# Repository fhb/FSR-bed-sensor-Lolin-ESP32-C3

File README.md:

# FSR-bed-sensor-Lolin-ESP32-C3
This project includes everything needed to build a bed occupancy sensor inspired by https://community.home-assistant.io/t/fsr-the-best-bed-occupancy-sensor/365795:
One PCB design for connecting two FSR sensors to an Lolin ESP32-C3 pico (pin compatible to Lolin ESP32-C3 mini) and a case for it. There are also two options to add a temperature sensor using the I2c port on the Lolin ESP32-C3. Everything has been tested and works. Make sure the JST-XH plugs are properly plugged in. 

List of materials:

* 2x JST_XH 2 pins male + female connector
* 1x Wemos Lolin ESP32-C3 pico
* 2x 8er Pinleiste
* 2x 8er Buchsenleiste
* 2x RM063 Potentiometer (V2)
* 2x FSR SF15-600 10kg

Option 1:The Wemos SHT-30 is the easiest option as ready made SH1.0 4Pin cables are available, that's the option I ended up using and designing a case for.
* 1x Wemos SHT-30 (https://www.wemos.cc/en/latest/d1_mini_shield/sht30.html)
* I2C Cable 10cm für LOLIN (WEMOS) SH1.0 4Pins

Option 2: You could also make your own JST-XH to JST-SH1.0 cable and solder a JST-XH connector to a BME280 5V Board. 
* JST-SH1.0 male connector --- 4 wire ---  JST-XH female + male connector 
* BME280 5V Board (I2C)

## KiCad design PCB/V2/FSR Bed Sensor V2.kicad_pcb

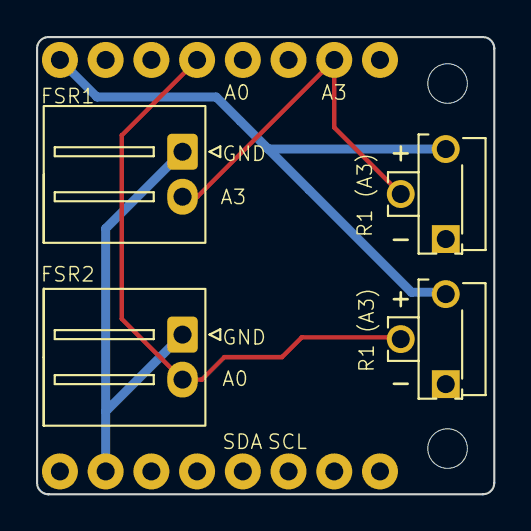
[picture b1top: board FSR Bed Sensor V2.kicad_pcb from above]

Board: 2 copper layers, 25.4 x 25.4 mm, 5 parts (0 on the bottom side), 4 nets.

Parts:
FSR1: ST_XH_S2B-XH-A-1_1x02_P2.50mm_Horizontal; JST_XH_S2B-XH-A-1_1x02_P2.50mm_Horizontal
FSR2: JST_XH_S2B-XH-A-1_1x02_P2.50mm_Horizontal
R1 (A3), R1 (A3)#2: Potentiometer_Runtron_RM-063_Horizontal
Wemos LOLIN C3 Pico: ESP32-C3; WEMOS_Lolin_ESP32-C3_Pico

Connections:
3.3V: R1 (A3).1, R1 (A3)#2.1, Wemos LOLIN C3 Pico.8
A0: FSR2.2, R1 (A3).2, Wemos LOLIN C3 Pico.5
A3: FSR1.2, R1 (A3)#2.2, Wemos LOLIN C3 Pico.2
GND: FSR1.1, FSR2.1, Wemos LOLIN C3 Pico.10

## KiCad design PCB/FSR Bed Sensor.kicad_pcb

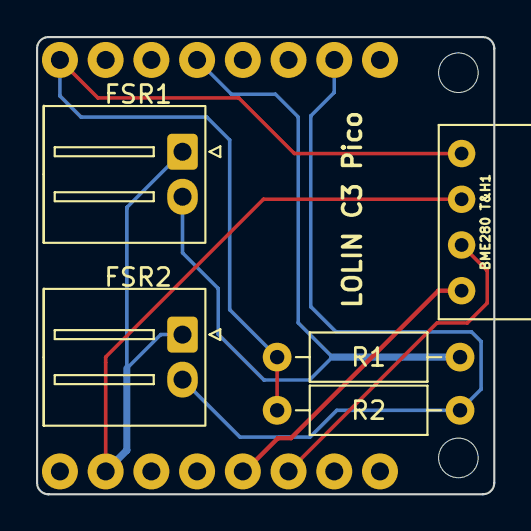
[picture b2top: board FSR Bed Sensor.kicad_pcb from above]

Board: 2 copper layers, 25.4 x 25.4 mm, 6 parts (0 on the bottom side), 6 nets.

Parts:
BME280 T&H1: BME280 5V
FSR1: ST_XH_S2B-XH-A-1_1x02_P2.50mm_Horizontal; JST_XH_S2B-XH-A-1_1x02_P2.50mm_Horizontal
FSR2: JST_XH_S2B-XH-A-1_1x02_P2.50mm_Horizontal
LOLIN C3 Pico: ESP32-C3; WEMOS_Lolin_ESP32-C3_Pico
R1, R2: 128kOhm; R_Axial_DIN0207_L6.3mm_D2.5mm_P10.16mm_Horizontal

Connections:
3.3V: BME280 T&H1.1, LOLIN C3 Pico.8, R1.1, R2.1
A0: FSR1.2, LOLIN C3 Pico.5, R1.2
A3: FSR2.2, LOLIN C3 Pico.2, R2.2
GND: BME280 T&H1.2, FSR1.1, FSR2.1, LOLIN C3 Pico.10
SCL: BME280 T&H1.3, LOLIN C3 Pico.14
SDA: BME280 T&H1.4, LOLIN C3 Pico.13

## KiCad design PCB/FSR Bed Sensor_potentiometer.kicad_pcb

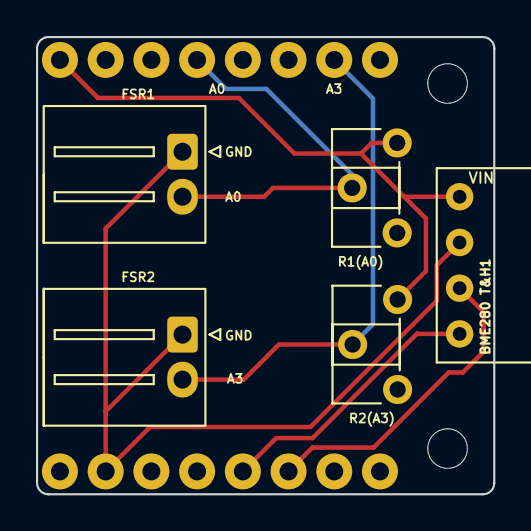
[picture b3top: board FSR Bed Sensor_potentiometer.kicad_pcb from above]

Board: 2 copper layers, 25.4 x 25.4 mm, 6 parts (0 on the bottom side), 6 nets.

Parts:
BME280 T&H1: BME280 5V
FSR1: ST_XH_S2B-XH-A-1_1x02_P2.50mm_Horizontal; JST_XH_S2B-XH-A-1_1x02_P2.50mm_Horizontal
FSR2: JST_XH_S2B-XH-A-1_1x02_P2.50mm_Horizontal
R1(A0), R2(A3): Potentiometer_ACP_CA6-H2,5_Horizontal
Wemos LOLIN C3 Pico: ESP32-C3; WEMOS_Lolin_ESP32-C3_Pico

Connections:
3.3V: BME280 T&H1.1, R1(A0).3, R2(A3).3, Wemos LOLIN C3 Pico.8
A0: FSR1.2, R1(A0).2, Wemos LOLIN C3 Pico.5
A3: FSR2.2, R2(A3).2, Wemos LOLIN C3 Pico.2
GND: BME280 T&H1.2, FSR1.1, FSR2.1, Wemos LOLIN C3 Pico.10
SCL: BME280 T&H1.3, Wemos LOLIN C3 Pico.14
SDA: BME280 T&H1.4, Wemos LOLIN C3 Pico.13

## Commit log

2023-01-21 Add files via upload
    corrected the edge cut and added M2 mounting holes at the corners
2023-01-21 Add files via upload
    cleanup
2023-02-17 Add files via upload
    switched to CA6-H2,5 potentiometers
2023-02-17 Add files via upload
    one option with normal resistors and one with CA6 potentiometers
2023-02-24 Create test
2023-02-24 Create text
2023-02-24 Create V2
2023-02-24 V2 with RM063 and without BME280 on the board
2023-02-25 Create styl
